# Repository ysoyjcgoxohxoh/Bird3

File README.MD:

# Bird 3 #

## Introduction ##
This repository attempts to document the specs and operation of the Bird 3 scooter. It provides a PCB design and associated software for a drop-in replacement Bird Brain compatible with the EA00004 and EA00022 brains.

The PCB is designed in KiCad around an ESP32-S3. It is designed to fit into the original enclosure and use the existing LCD, the [TXW154028S0](./Datasheets/TXW154028S0_SPEC.pdf).

More documentation for the scooter is available in the [Wiki](../../wiki).

> [!WARNING]
> This repository is intended for use with legally and ethically acquired scooters only. Not only is stealing scooters a crime, it is also unethical.

## Repository Structure ##
- The `Arduino` directory contains the code to run the scooter.
- The `Datasheets` directory contains datasheets for various components.
- The `PCB` directory contains the PCB design.
  - [Rev 1](./PCB/Bird3Controller_Rev1/Readme.md).
  - [Rev 2](./PCB/Bird3Controller_Rev2/Readme.md).
  - [Rev 3](./PCB/Bird3Controller_Rev3/Readme.md).

## Credits ##
- `Mental_Metalhead` - For lots of back and forth testing the software, providing the 22-pin connector pinout, and for various advice on designing PCBs.
- The folks in the Scooterhacking.org community. (DM me if you wish to be credited directly. You know who you are.)

## Board Renderings - Rev 2 ##

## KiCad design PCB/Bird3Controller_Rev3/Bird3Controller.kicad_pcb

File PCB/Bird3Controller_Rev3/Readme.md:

> [!NOTE]
> This design has been assembled and is working with no errata discovered yet.

## Development ##
This was developed in [KiCad 8](https://www.kicad.org/), a FOSS EDA suite. Most or all of the symbols, footprints, and 3D models have been included in the repo to reduce the chance of broken references.

## Ordering Information ##
[JLCPCB](https://jlcpcb.com/) is a good place from which to order a PCB.
- The gerber files are in the [./plots](plots) folder.
- The Bill of Materials is at [./BOM.csv](BOM.csv).

These JLCPCB settings were used for the order:
| Setting                 | Value                   |
|-------------------------|-------------------------|
| Layers                  | 2                       |
| Dimension               | 43 mm * 108 mm          |
| PCB Thickness           | 1.6                     |
| Impedance Control       | no                      |
| Material Type           | FR4-Standard TG 135-140 |
| Via Covering            | Tented                  |
| Outer Copper Weight     | 1 oz                    |
| Castellated Holes       | no                      |
| Edge Plating            | no                      |
| Remove Order Number     | Specify a location      |
| Board Outline Tolerance | ±0.2mm(Regular)         |

## Fixes from Rev 2 ##
- TBA

## Improvements from Rev 2 ##
- TBA

## Errata ##
- TBA

## Bill of Materials ##
An interactive BOM generated by [InteractiveHtmlBOM](https://github.com/openscopeproject/InteractiveHtmlBom) is available at [https://html-preview.github.io/?url=https://github.com/ysoyjcgoxohxoh/Bird3/blob/master/PCB/Bird3Controller_Rev3/bom/ibom.html](https://html-preview.github.io/?url=https://github.com/ysoyjcgoxohxoh/Bird3/blob/master/PCB/Bird3Controller_Rev3/bom/ibom.html)

## PDF Schematic ##
A PDF schematic is available at [Bird3Controller.pdf](Bird3Controller.pdf). When opened in a more advanced viewer such as Acrobat Reader, the components are bookmarked, and both components and nets are clickable as shown in this screenshot, making it easy to open the part's datasheet or Mouser.com listing.

## PNG Schematic ##

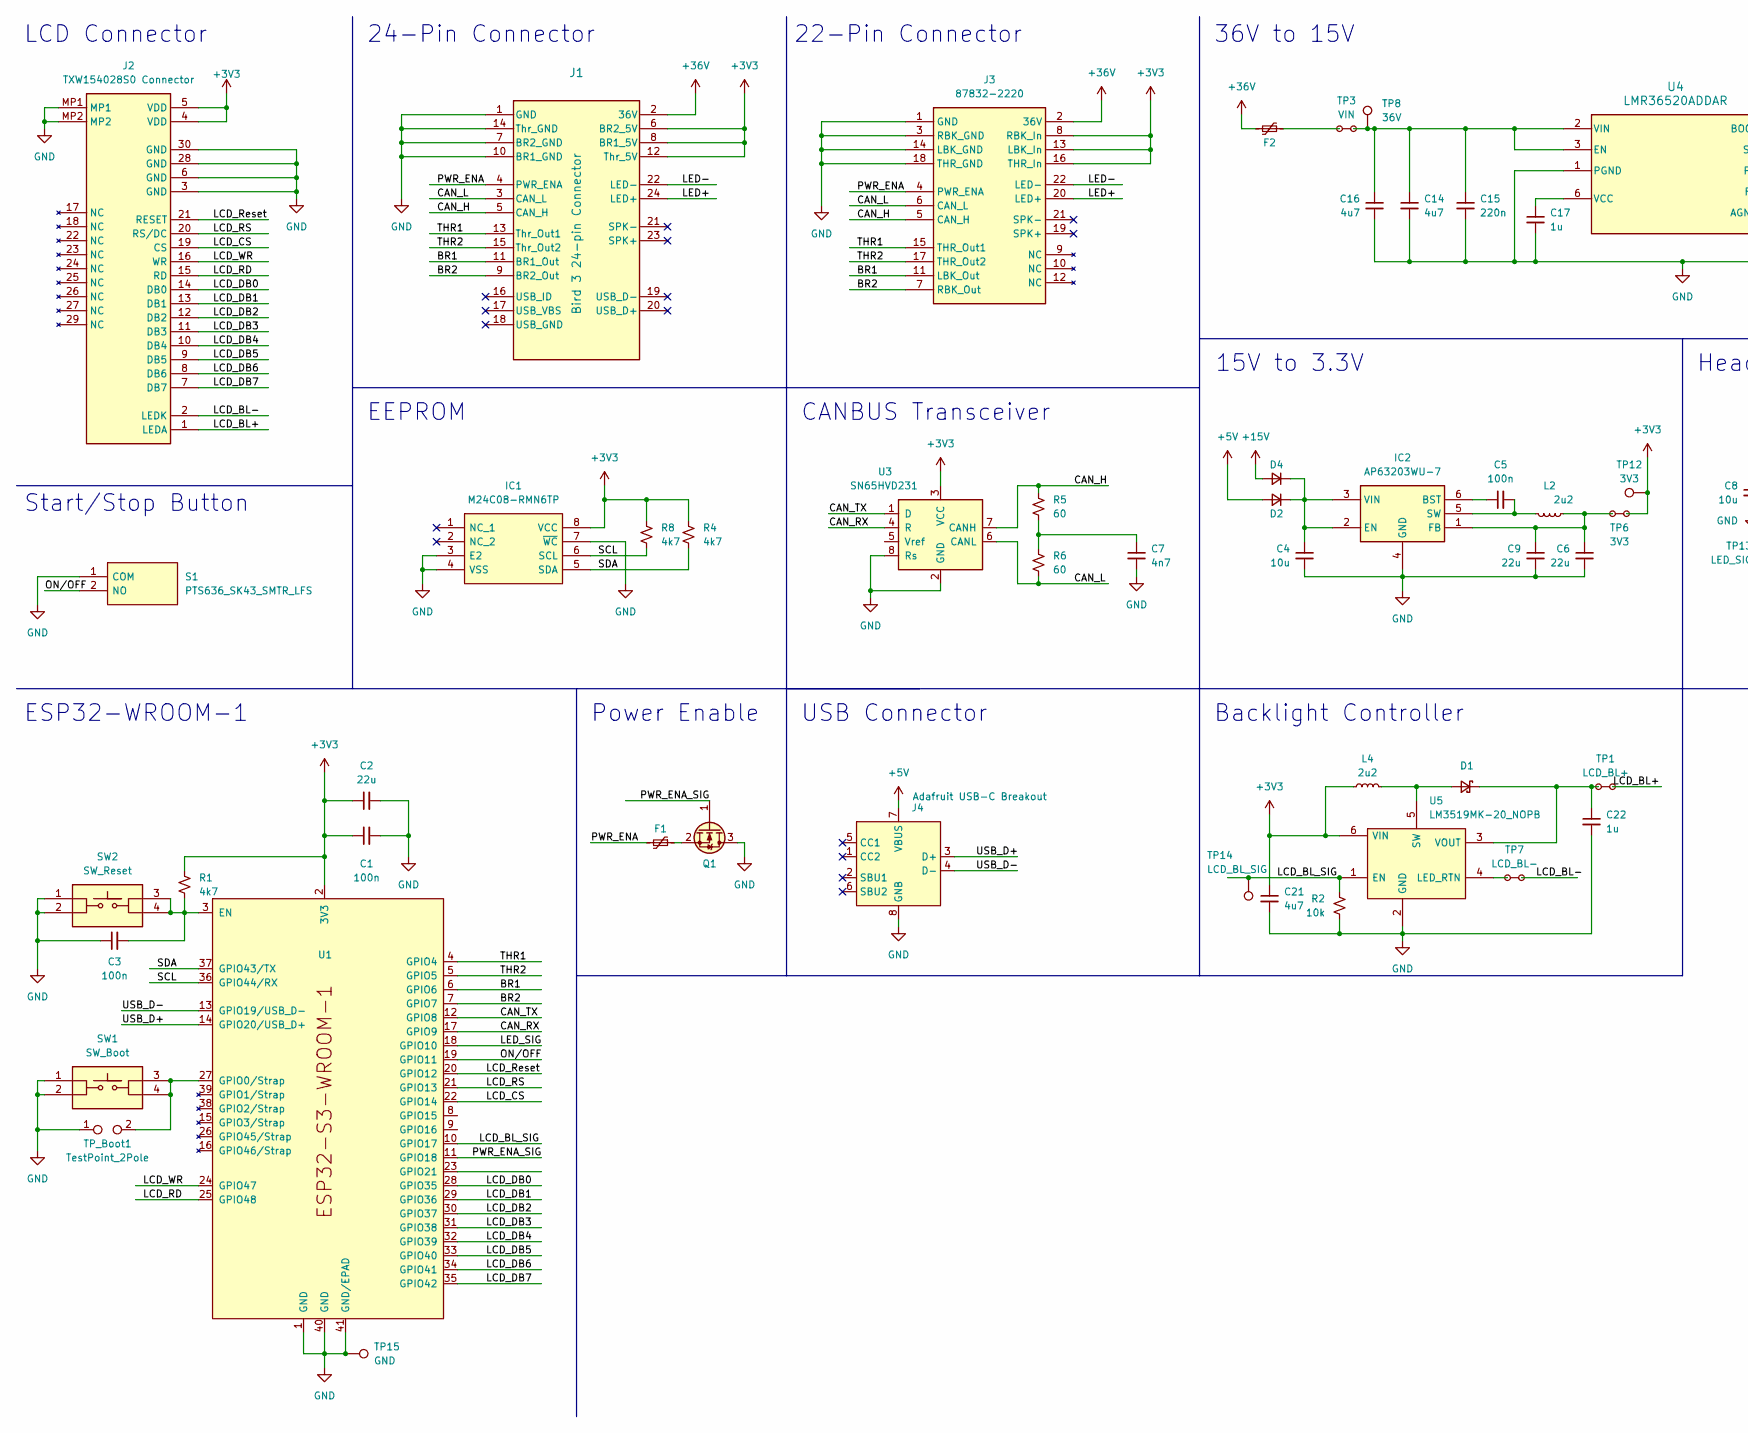
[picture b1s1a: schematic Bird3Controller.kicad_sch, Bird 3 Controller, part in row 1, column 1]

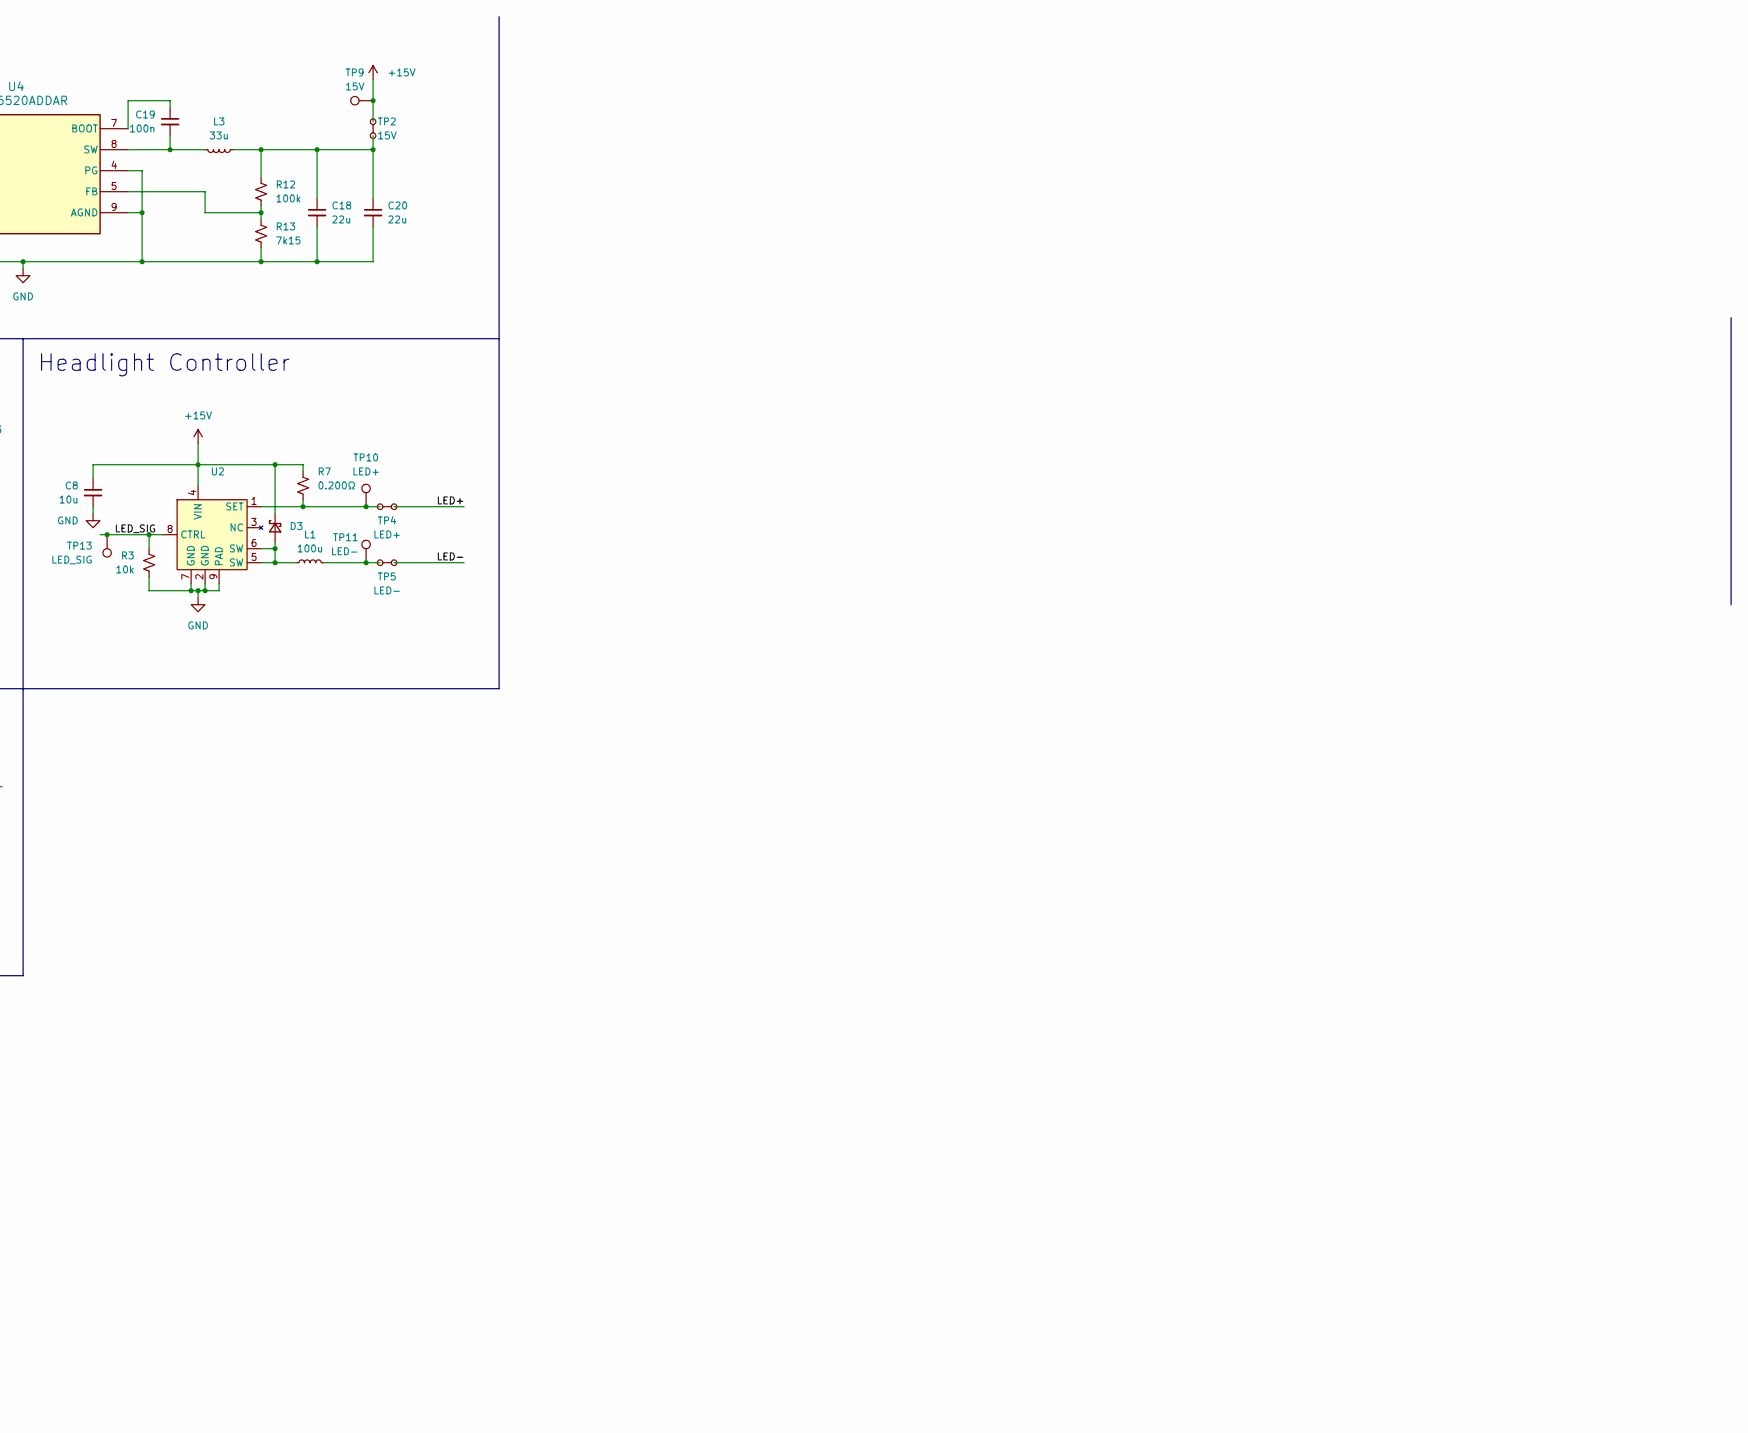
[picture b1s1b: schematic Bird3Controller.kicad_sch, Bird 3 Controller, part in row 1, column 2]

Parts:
C1, C3, C5, C19: 100n; C_0805_2012Metric; Rating 50V; mouser# 581-KGM21NR71H104KT; Digikey Part Number 13-AC0805JRX7R9BB104CT-ND
C2: 22u; C_0805_2012Metric; Rating 16V; mouser# 81-GRT21BR61C226ME3L; Digikey Part Number 490-12383-1-ND
C4, C8: 10u; C_0805_2012Metric; Rating 25V; mouser# 81-GRT21BC71E106KE13; Digikey Part Number 490-GRT21BC71E106KE13LCT-ND
C6, C9: 22u; C_0805_2012Metric; Rating 6.3V; mouser# 187-CL21A226MQQNNNE; Mouser Price QTY1 0.13
C7: 4n7; C_0805_2012Metric; Rating 50V; mouser# 581-08055C472K4T4A; Digikey Part Number 478-KAM21KR71E224KUCT-ND
C14, C16, C21: 4u7; C_1210_3225Metric; Rating 50V; mouser# 187-CL32B475KBUYNNE; Digikey Part Number 1276-CL32Y475KCIVPNECT-ND
C15: 220n; C_0805_2012Metric; Rating 50V; mouser# 187-CL21B224KBFNNNG; Digikey Part Number 478-KAM21KR71E224KUCT-ND
C17, C22: 1u; C_0805_2012Metric; Rating 50V; mouser# 187-CL21B105KBFNNNE; Digikey Part Number 1276-1029-1-ND
C18: 22u; C_0805_2012Metric; Rating 25V; mouser# 187-CL21A226MAYNNWE; Mouser Price QTY1 0.32
C20: 22u; C_0805_2012Metric; Rating 25V; mouser# 187-CL21A226MAYNNWE; Digikey Part Number 1276-CL21A107MQYNNWECT-ND
D1, D3: D_Schottky_Small; D_0805_2012Metric; Rating 20V; mouser# 581-SD0805S020S1R0; Digikey Part Number 478-7800-1-ND
D2, D4: GS1J_R1_00001; DIOM5027X244M; Rating 600V; mouser# 241-GS1J_R1_00001; Digikey Part Number 3757-GS1J_R1_00001CT-ND
F1: Polyfuse_Small; FUSC1607X85N; Rating 60V; mouser# 530-0ZCM0001FF2G; Mouser Price QTY1 0.19
F2: 0ZCF0100AF2A; FUSC7451X170N; Rating 60V; mouser# 530-0ZCF0100AF2A; Mouser Price QTY1 0.55
IC1: M24C08-RMN6TP; SOIC127P600X175-8N; Rating 5.5V; mouser# 511-M24C08-RMN6TP; Mouser Price QTY1 0.19
IC2: AP63203WU-7; AP63203WU7; Rating 32V; mouser# 621-AP63203WU-7; Mouser Price QTY1 0.87
J1: Bird 3 24-pin Connector; CONN_87832-2420_MOL; Rating 125V, 2A; mouser# 538-87832-6123; Digikey Part Number WM18646-ND
J2: TXW154028S0 Connector; FH34SRJ30S05SH50; Rating 50V, 125mA; mouser# 798-FH34SRJ30S05SH50; Digikey Part Number HFT430CT-ND
J3: 87832-2220; 878322220; Rating 125V, 2A; mouser# 538-87832-6062; Mouser Price QTY1 3.27
J4: Adafruit USB-C Breakout; mouser# 485-4090; Mouser Price QTY1 2.95
L1: 100u; SRR1240270M; Rating 1.2A, 300mOhms; mouser# 652-SRR1240-101M; Digikey Part Number SRR1240-101MCT-ND
L2: 2u2; INDC2520X120N; Rating 2.2A, 90mOhms; mouser# 963-MAMK2520H2R2M; Mouser Price QTY1 0.23
L3: 33u; INDPM7973X540N; Rating 4A, 127.6mOhms; mouser# 652-SRP7050WA-330M; Mouser Price QTY1 0.88
L4: 2u2; INDC2520X100N; Rating 1.3A, 80mOhms; mouser# 652-CVH252009-2R2M; Digikey Part Number CVH252009-2R2MCT-ND
Q1: 2N7002A; TSOT-23; Rating 60V, 280mA, 2 Ohms; mouser# 637-2N7002A; Mouser Price QTY1 0.11
R1, R4, R8: 4k7; R_0805_2012Metric; Rating 150v, 125mW; mouser# 71-CRCW0805J-4.7K-E3; Digikey Part Number 541-4.7KACT-ND
R2, R3: 10k; R_0805_2012Metric; Rating 150v, 125mW; mouser# 71-CRCW0805J-10K-E3; Mouser Price QTY1 0.10
R5, R6: 60; R_0805_2012Metric; Rating 150v, 500mW; mouser# 71-RCS080560R4FKEA; Digikey Part Number 541-RCS080560R4FKEACT-ND
R7: 0.200Ω; R_0805_2012Metric; Rating 125mW; mouser# 279-RLC73K2AR20FTDF; Mouser Price QTY1 0.26
R12: 100k; R_0805_2012Metric; Rating 150v, 500mW; mouser# 71-RCS0805100KFKEA; Digikey Part Number 541-2850-1-ND
R13: 7k15; R_0805_2012Metric; Rating 150v, 500mW; mouser# 71-CRCW08057K15FKEAC; Mouser Price QTY1 0.11
S1: PTS636_SK43_SMTR_LFS; PTS636SK43SMTRLFS; Rating 12V, 50mA; mouser# 611-PTS636SK43SMTRLF; Digikey Part Number CKN12311-1-ND
SW1: SW_Boot; PTS526SK15SMTR2LFS; Rating 12V, 50mA; mouser# 611-PTS526SK15SMR2L; Digikey Part Number CKN12221-1-ND
SW2: SW_Reset; PTS526SK15SMTR2LFS; Rating 12V, 50mA; mouser# 611-PTS526SK15SMR2L; Digikey Part Number CKN12221-1-ND
TP1: LCD_BL+; TestPointBridge_2Pads_D1.5mm
TP2: 15V; TestPointBridge_2Pads_D1.5mm
TP3: VIN; TestPointBridge_2Pads_D1.5mm
TP4: LED+; TestPointBridge_2Pads_D1.5mm
TP5: LED-; TestPointBridge_2Pads_D1.5mm
TP6: 3V3; TestPointBridge_2Pads_D1.5mm
TP7: LCD_BL-; TestPointBridge_2Pads_D1.5mm
TP8: 36V; Labeled_TestPoint_1.5mm
TP9: 15V; Labeled_TestPoint_1.5mm
TP10: LED+; Labeled_TestPoint_1.5mm
TP11: LED-; Labeled_TestPoint_1.5mm
TP12: 3V3; Labeled_TestPoint_1.5mm
TP13: LED_SIG; Labeled_TestPoint_1.5mm
TP14: LCD_BL_SIG; Labeled_TestPoint_1.5mm
TP15: GND; Labeled_TestPoint_1.5mm
TP_Boot1: TestPoint_2Pole; TestPoint_2Pads_D1.0mm
U1: ESP32-S3-WROOM-1; Rating 3.6V; mouser# 356-EP32S3WROOM1N8R8; Digikey Part Number 1965-ESP32-S3-WROOM-1-N8R8CT-ND
U2: Diodes_SO-8EP; Rating 60V; mouser# 621-AL8862SP-13; Mouser Price QTY1 0.93
U3: SN65HVD231; SOIC-8_3.9x4.9mm_P1.27mm; Rating 3.6V; mouser# 595-SN65HVD231DRG4; Digikey Part Number 296-15380-1-ND
U4: LMR36520ADDAR; SOIC127P600X170-9N; Rating 65V; mouser# 595-LMR36520ADDAR; Digikey Part Number 296-LMR36520ADDARCT-ND
U5: LM3519MK-20_NOPB; SOT95P280X110-6N; Rating 5.5V; mouser# 926-LM3519MK-20/NOPB; Digikey Part Number 296-43568-1-ND

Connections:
+3V3: C1.1, C2.1, C21.1, IC1.8 (VCC), J1.6 (BR2_5V), J1.8 (BR1_5V), J1.12 (Thr_5V), J2.4 (VDD), J2.5 (VDD), J3.8 (RBK_In), J3.13 (LBK_In), J3.16 (THR_In), L4.1, R1.2, R4.2, R8.1, TP6.2 (1), TP12.1, U1.2 (3V3), U3.3 (VCC), U5.6 (VIN)
+5V: D2.2 (A), J4.7 (VBUS)
+15V: C8.1, D3.1 (K), D4.2 (A), R7.1, TP2.1, TP9.1, U2.4 (VIN)
+36V: F2.1, J1.2 (36V), J3.2 (36V)
/BR1: J1.11 (BR1_Out), J3.11 (LBK_Out), U1.6 (GPIO6)
/BR2: J1.9 (BR2_Out), J3.7 (RBK_Out), U1.7 (GPIO7)
/CAN_H: J1.5 (CAN_H), J3.5 (CAN_H), R5.1, U3.7 (CANH)
/CAN_L: J1.3 (CAN_L), J3.6 (CAN_L), R6.2, U3.6 (CANL)
/CAN_RX: U1.17 (GPIO9), U3.4 (R)
/CAN_TX: U1.12 (GPIO8), U3.1 (D)
/LCD_BL+: J2.1 (LEDA), TP1.1
/LCD_BL-: J2.2 (LEDK), TP7.1
/LCD_BL_SIG: R2.2, TP14.1, U1.10 (GPIO17), U5.1 (EN)
/LCD_CS: J2.19 (CS), U1.22 (GPIO14)
/LCD_DB0: J2.14 (DB0), U1.28 (GPIO35)
/LCD_DB1: J2.13 (DB1), U1.29 (GPIO36)
/LCD_DB2: J2.12 (DB2), U1.30 (GPIO37)
/LCD_DB3: J2.11 (DB3), U1.31 (GPIO38)
/LCD_DB4: J2.10 (DB4), U1.32 (GPIO39)
/LCD_DB5: J2.9 (DB5), U1.33 (GPIO40)
/LCD_DB6: J2.8 (DB6), U1.34 (GPIO41)
/LCD_DB7: J2.7 (DB7), U1.35 (GPIO42)
/LCD_RD: J2.15 (RD), U1.25 (GPIO48)
/LCD_RS: J2.20 (RS/DC), U1.21 (GPIO13)
/LCD_Reset: J2.21 (RESET), U1.20 (GPIO12)
/LCD_WR: J2.16 (WR), U1.24 (GPIO47)
/LED+: J1.24 (LED+), J3.20 (LED+), TP4.2 (1)
/LED-: J1.22 (LED-), J3.22 (LED-), TP5.2 (1)
/LED_SIG: R3.2, TP13.1, U1.18 (GPIO10), U2.8 (CTRL)
/ON/OFF: S1.2 (NO), U1.19 (GPIO11)
/PWR_ENA: F1.2, J1.4 (PWR_ENA), J3.4 (PWR_ENA)
/PWR_ENA_SIG: Q1.1 (G), U1.11 (GPIO18)
/SCL: IC1.6 (SCL), R8.2, U1.36 (GPIO44/RX)
/SDA: IC1.5 (SDA), R4.1, U1.37 (GPIO43/TX)
/THR1: J1.13 (Thr_Out1), J3.15 (THR_Out1), U1.4 (GPIO4)
/THR2: J1.15 (Thr_Out2), J3.17 (THR_Out2), U1.5 (GPIO5)
/USB_D+: J4.3 (D+), U1.14 (GPIO20/USB_D+)
/USB_D-: J4.4 (D-), U1.13 (GPIO19/USB_D-)
GND: C1.2, C2.2, C3.1, C4.2, C6.2, C7.2, C8.2, C9.2, C14.2, C15.2, C16.2, C17.2, C18.2, C20.2, C21.2, C22.2, IC1.3 (E2), IC1.4 (VSS), IC1.7 (~WC), IC2.4 (GND), J1.1 (GND), J1.7 (BR2_GND), J1.10 (BR1_GND), J1.14 (Thr_GND), J2.3 (GND), J2.6 (GND), J2.28 (GND), J2.30 (GND), J2.MP1, J2.MP2, J3.1 (GND), J3.3 (RBK_GND), J3.14 (LBK_GND), J3.18 (THR_GND), J4.8 (GNB), Q1.3 (D), R2.1, R3.1, R13.1, S1.1 (COM), SW1.1, SW1.2, SW2.1, SW2.2, TP15.1, TP_Boot1.1, U1.1 (GND), U1.40 (GND), U1.41 (GND/EPAD), U2.2 (GND), U2.7 (GND), U2.9 (PAD), U3.2 (GND), U3.8 (Rs), U4.1 (PGND), U4.4 (PG), U4.9 (AGND), U5.2 (GND)
unnamed: C7.1, R5.2, R6.1
unnamed: C18.1, C20.1, L3.2, R12.2, TP2.2 (1)
unnamed: D1.2 (A), L4.2, U5.5 (SW)
unnamed: C22.1, D1.1 (K), TP1.2 (1), U5.3 (VOUT)
unnamed: C4.1, D2.1 (K), D4.1 (K), IC2.2 (EN), IC2.3 (VIN)
unnamed: D3.2 (A), L1.1, U2.5 (SW), U2.6 (SW)
unnamed: F2.2, TP3.2 (1)
unnamed: C5.1, IC2.6 (BST)
unnamed: C6.1, C9.1, IC2.1 (FB), L2.2, TP6.1
unnamed: C5.2, IC2.5 (SW), L2.1
unnamed: L1.2, TP5.1, TP11.1
unnamed: F1.1, Q1.2 (S)
unnamed: C3.2, R1.1, SW2.3, SW2.4, U1.3 (EN)
unnamed: SW1.3, SW1.4, TP_Boot1.2, U1.27 (GPIO0/Strap)
unnamed: R7.2, TP4.1, TP10.1, U2.1 (SET)
unnamed: C19.1, U4.7 (BOOT)
unnamed: C14.1, C15.1, C16.1, TP3.1, TP8.1, U4.2 (VIN), U4.3 (EN)
unnamed: R12.1, R13.2, U4.5 (FB)
unnamed: C19.2, L3.1, U4.8 (SW)
unnamed: C17.1, U4.6 (VCC)
unnamed: TP7.2 (1), U5.4 (LED_RTN)

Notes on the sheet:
22-Pin Connector
Headlight Controller
15V to 3.3V
EEPROM
36V to 15V
Power Enable
ESP32-WROOM-1
CANBUS Transceiver
24-Pin Connector
LCD Connector
Backlight Controller
Start/Stop Button
USB Connector

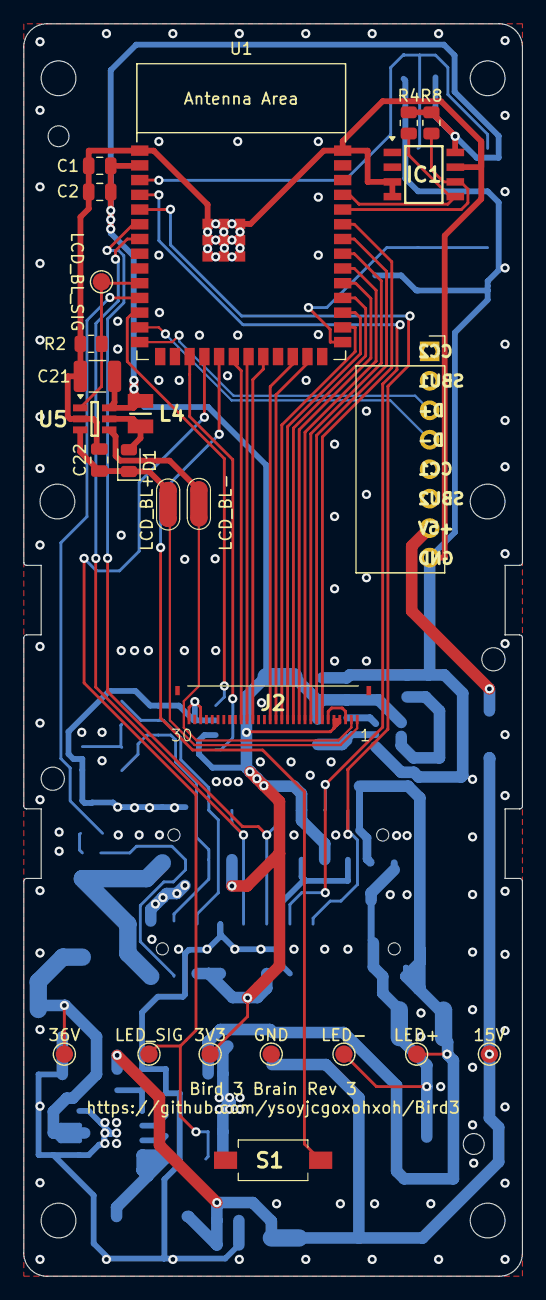
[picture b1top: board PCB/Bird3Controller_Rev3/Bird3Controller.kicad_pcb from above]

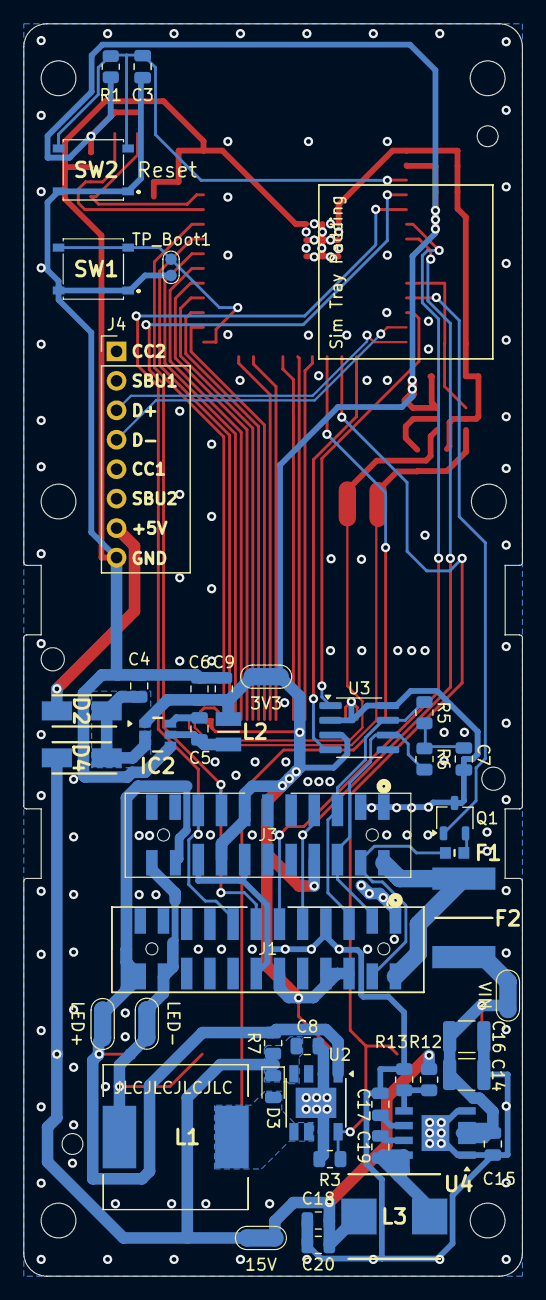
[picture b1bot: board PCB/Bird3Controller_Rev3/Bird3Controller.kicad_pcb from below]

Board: 2 copper layers, 43.0 x 108.0 mm, 69 parts (45 on the bottom side), 60 nets.

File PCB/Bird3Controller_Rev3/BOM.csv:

"Reference","Value","Rating","Description","Manufacturer_Name","Manufacturer_Part_Number","Mouser Part Number","Mouser Price/Stock","Qty","Mouser Price QTY1","Mouser Price QTY10"
"C1,C3,C5,C19","100n","50V","-- mixed values --","YAGEO","AC0805JRX7R9BB104","603-AC0805JX7R9BB104","https://www.mouser.com/ProductDetail/YAGEO/AC0805JRX7R9BB104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","4","0.10","0.065"
"C2","22u","16V","ESP32 Decoupling","Murata Electronics","GRT21BR61C226ME13L","81-GRT21BR61C226ME3L","https://www.mouser.com/ProductDetail/Murata-Electronics/GRT2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","1","0.39","0.196"
"C4,C8","10u","25V","5V/15V Decoupling","Murata Electronics","GRT21BC71E106KE13L","81-GRT21BC71E106KE13","https://www.mouser.com/ProductDetail/Murata-Electronics/GRT2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","2","0.35","0.199"
"C6,C9","22u","6.3V","3V3 Output Filtering","Samsung Electro-Mechanics","CL21A226MQQNNNE","187-CL21A226MQQNNNE","https://www.mouser.com/ProductDetail/Samsung-Electro-Mechani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","2","0.13","0.053"
"C7","4n7","50V","CANBUS Split Termination","KYOCERA AVX","08055C472K4T4A","581-08055C472K4T4A","https://www.mouser.com/ProductDetail/KYOCERA-AVX/08055C472K4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","1","0.10","0.058"
"C14,C16,C21","4u7","50V","-- mixed values --","Samsung Electro-Mechanics","CL32Y475MCIVPNE","187-CL32B475KBUYNNE","https://www.mouser.com/ProductDetail/Samsung-Electro-Mechani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","3","0.36","0.179"
"C15","220n","50V","36V Decoupling","Samsung Electro-Mechanics","CL21B224KBFNNNG","187-CL21B224KBFNNNG","https://www.mouser.com/ProductDetail/Samsung-Electro-Mechani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","1","0.10","0.02"
"C17,C22","1u","50V","LCD Backlight Output Cap","Samsung Electro-Mechanics","CL21B105MBFNNNE","187-CL21B105MBFNNNE","https://www.mouser.com/ProductDetail/Samsung-Electro-Mechani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","2","0.10","0.027"
"C18,C20","22u","25V","15V Output Cap","Samsung Electro-Mechanics","CL21A226MAYNNNE","187-CL21A226MAYNNNE","https://www.mouser.com/ProductDetail/Samsung-Electro-Mechani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","2","0.25","0.115"
"D1,D3","D_Schottky_Small","20V","Freewheeling Diode","KYOCERA AVX","SD0805S020S1R0","581-SD0805S020S1R0","https://www.mouser.com/ProductDetail/KYOCERA-AVX/SD0805S020S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","2","0.32","0.252"
"D2,D4","GS1J_R1_00001","600V","15V input diode","PANJIT","GS1J_R1_00001","241-GS1J_R1_00001","https://www.mouser.com/ProductDetail/Panjit/GS1J_R1_00001?qs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","2","0.21","0.148"
"F1","Polyfuse_Small","60V","PWR_ENA Fuse","Bel Fuse","0ZCM0001FF2G","530-0ZCM0001FF2G","https://www.mouser.com/ProductDetail/Bel-Fuse/0ZCM0001FF2G?q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","1","0.19","0.16"
"F2","0ZCF0100AF2A","60V","VIN Fuse","BelFuse","0ZCF0100AF2A","530-0ZCF0100AF2A","https://www.mouser.com/ProductDetail/Bel-Fuse/0ZCF0100AF2A?q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","1","0.55","0.454"
"IC1","M24C08-RMN6TP","5.5V","EEPROM","STMicroelectronics","M24C08-RMN6TP","511-M24C08-RMN6TP","https://www.mouser.com/ProductDetail/STMicroelectronics/M24C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","1","0.19","0.175"
"IC2","AP63203WU-7","32V","3V3 Switching Regulator","Diodes Incorporated","AP63203WU-7","621-AP63203WU-7","https://www.mouser.com/ProductDetail/Diodes-Incorporated/AP6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","1","0.87","0.71"
"J1","Bird 3 24-pin Connector","125V, 2A","24-Pin Connector","Molex","87832-6123","538-87832-6123","https://www.mouser.com/ProductDetail/Molex/87832-6123?qs=Vr3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","1","2.05","1.79"
"J2","TXW154028S0 Connector","50V, 125mA","LCD Connector","Hirose","FH34SRJ-30S-0.5SH(50)","798-FH34SRJ30S05SH50","https://www.mouser.com/ProductDetail/Hirose-Connector/FH34SR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","1","1.24","1.05"
"J3","87832-2220","125V, 2A","22-Pin Connector","Molex","87832-6062","538-87832-6062","https://www.mouser.com/ProductDetail/Molex/87832-6062?qs=yd8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","1","3.27","2.98"
"J4","Adafruit USB-C Breakout","","USB-C Breakout","Adafruit","4090","485-4090","https://www.mouser.com/ProductDetail/Adafruit/4090?qs=2WXlat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","1","2.95","2.95"
"L1","100u","1.2A, 300mOhms","Headlight Inductor","Bourns","SRR1240-101M","652-SRR1240-101M","https://www.mouser.com/ProductDetail/Bourns/SRR1240-101M?qs=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","1","0.64","0.634"
"L2","2u2","2.2A, 90mOhms","3.3V Inductor","TAIYO YUDEN","MAMK2520H2R2M","963-MAMK2520H2R2M","https://www.mouser.com/ProductDetail/TAIYO-YUDEN/MAMK2520H2R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","1","0.23","0.158"
"L3","33u","4A, 127.6mOhms","15V Inductor","Bourns","SRP7050WA-330M","652-SRP7050WA-330M","https://www.mouser.com/ProductDetail/Bourns/SRP7050WA-330M?q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","1","0.88","0.757"
"L4","2u2","1.3A, 80mOhms","Backlight Inductor","Bourns","CVH252009-2R2M","652-CVH252009-2R2M","https://www.mouser.com/ProductDetail/Bourns/CVH252009-2R2M?q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","1","0.11","0.107"
"Q1","2N7002A","60V, 280mA, 2 Ohms","PWR_ENA Transistor","Diotec","2N7002A","637-2N7002A","https://www.mouser.com/ProductDetail/Diotec-Semiconductor/2N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","1","0.11","0.081"
"R1,R4,R8","4k7","150v, 125mW","-- mixed values --","Vishay / Dale","CRCW08054K70JNEA","71-CRCW0805J-4.7K-E3","https://www.mouser.com/ProductDetail/Vishay-Dale/CRCW08054K7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","3","0.10","0.02"
"R2,R3","10k","150v, 125mW","-- mixed values --","Vishay / Dale","CRCW080510K0JNEA","71-CRCW0805J-10K-E3","https://www.mouser.com/ProductDetail/Vishay-Dale/CRCW080510K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","2","0.10","0.019"
"R5,R6","60","150v, 500mW","CANBUS Termination","Vishay / Dale","RCS080560R4FKEA","71-RCS080560R4FKEA","https://www.mouser.com/ProductDetail/Vishay-Dale/RCS080560R4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","2","0.13","0.043"
"R7","0.200Ω","125mW","Current Sense","TE Connectivity / CGS","RLC73K2AR20FTDF","279-RLC73K2AR20FTDF","https://www.mouser.com/ProductDetail/TE-Connectivity-CGS/RLC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","1","0.26","0.221"
"R12","100k","150v, 500mW","15V Voltage Set Divider","Vishay / Dale","RCS0805100KFKEA","71-RCS0805100KFKEA","https://www.mouser.com/ProductDetail/Vishay-Dale/RCS0805100K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","1","0.13","0.063"
"R13","7k15","150v, 500mW","15V Voltage Set Divider","Vishay / Dale","CRCW08057K15FKEAC","71-CRCW08057K15FKEAC","https://www.mouser.com/ProductDetail/Vishay-Dale/CRCW08057K1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","1","0.11","0.029"
"S1","PTS636_SK43_SMTR_LFS","12V, 50mA","Start/Stop Button","C & K COMPONENTS","PTS636 SK43 SMTR LFS","611-PTS636SK43SMTRLF","https://www.mouser.com/ProductDetail/CK/PTS636-SK43-SMTR-LFS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","1","0.16","0.148"
"SW1,SW2","-- mixed values --","12V, 50mA","-- mixed values --","C & K COMPONENTS","PTS526 SK15 SMTR2 LFS","611-PTS526SK15SMR2L","https://www.mouser.com/ProductDetail/CK/PTS526-SK15-SMTR2-LF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","2","0.14","0.13"
"TP8,TP9,TP10,TP11,TP12,TP13,TP14,TP15","-- mixed values --","","test point","","","","","8","",""
"U1","ESP32-S3-WROOM-1","3.6V","Microcontroller","Espressif Systems","ESP32-S3-WROOM-1-N8R8","356-EP32S3WROOM1N8R8","https://www.mouser.com/ProductDetail/Espressif-Systems/ESP32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","1","3.62","3.62"
"U2","~","60V","Headlight Driver","Diodes","AL8862SP-13","621-AL8862SP-13","https://www.mouser.com/ProductDetail/Diodes-Incorporated/AL8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","1","0.93","0.748"
"U3","SN65HVD231","3.6V","CANBUS Driver","Texas Instruments","SN65HVD231DRG4","595-SN65HVD231DRG4","https://www.mouser.com/ProductDetail/Texas-Instruments/SN65H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","1","2.51","2.25"
"U4","LMR36520ADDAR","65V","15V Switching Regulator","Texas Instruments","LMR36520ADDAR","595-LMR36520ADDAR","https://www.mouser.com/ProductDetail/Texas-Instruments/LMR36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","1","2.72","2.39"
"U5","LM3519MK-20_NOPB","5.5V","Backlight Driver","Texas Instruments","LM3519MK-20/NOPB","926-LM3519MK-20/NOPB","https://www.mouser.com/ProductDetail/Texas-Instruments/LM351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","1","2.02","1.72"
